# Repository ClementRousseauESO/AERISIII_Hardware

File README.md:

# AERISIII_Hardware
KiCad projects for AERISIII boards

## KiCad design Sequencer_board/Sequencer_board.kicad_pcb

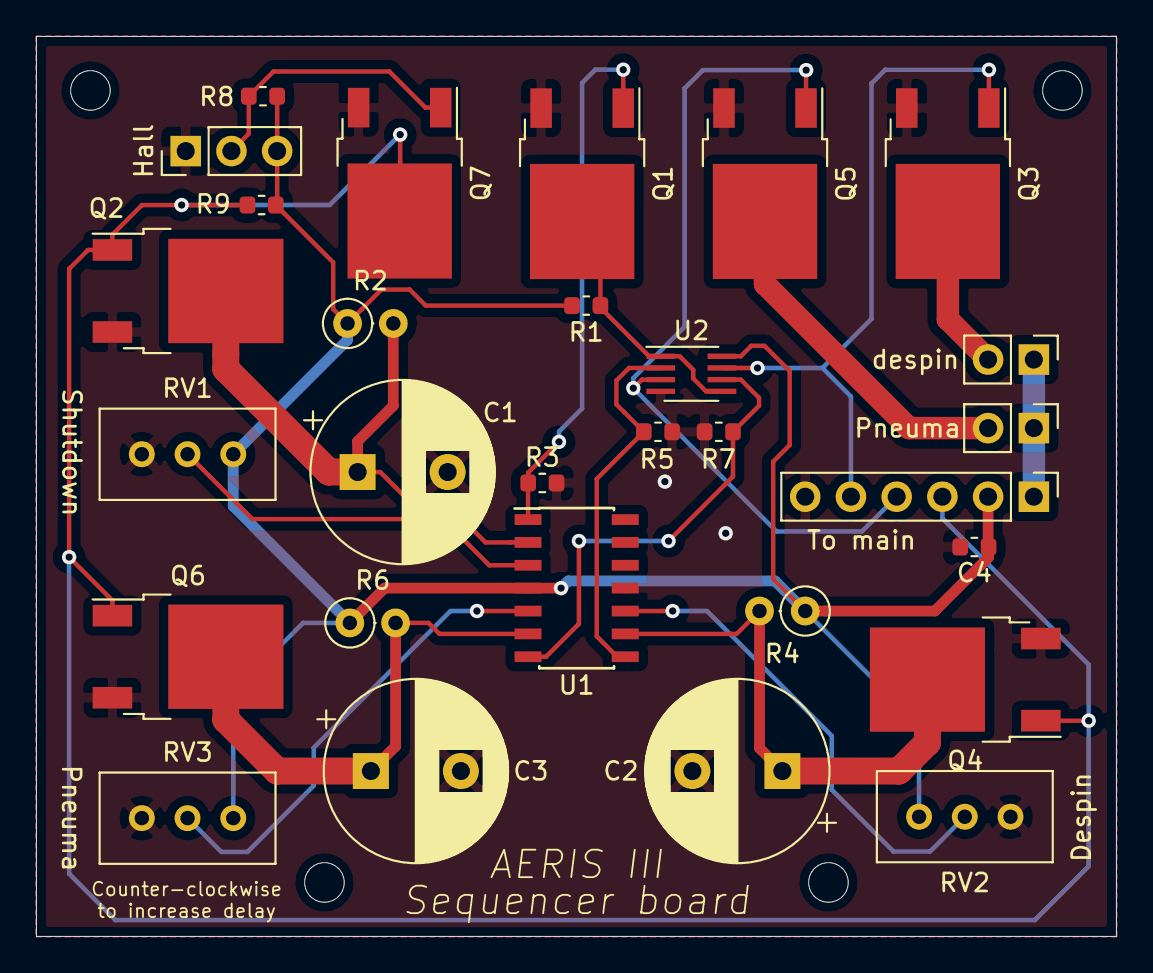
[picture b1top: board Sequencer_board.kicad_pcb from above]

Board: 2 copper layers, 60.0 x 50.0 mm, 29 parts (0 on the bottom side), 19 nets.

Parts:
C1, C2, C3: 470u; CP_Radial_D10.0mm_P5.00mm
C4: 100n; C_0603_1608Metric
Hall: Conn_01x03; PinHeader_1x03_P2.54mm_Vertical
Pneuma: Conn_01x02; PinHeader_1x02_P2.54mm_Vertical
Q1, Q2, Q3, Q4, Q5, Q6, Q7: Q_NMOS_GDS; TO-252-2
R1, R8, R9: 10k; R_0603_1608Metric
R2: 56k; R_Axial_DIN0207_L6.3mm_D2.5mm_P2.54mm_Vertical
R3, R5, R7: 100k; R_0603_1608Metric
R4: 33k; R_Axial_DIN0207_L6.3mm_D2.5mm_P2.54mm_Vertical
R6: 18k; R_Axial_DIN0207_L6.3mm_D2.5mm_P2.54mm_Vertical
RV1, RV2, RV3: 10k; Potentiometer_Bourns_3296W_Vertical
To main: Conn_01x06; PinHeader_1x06_P2.54mm_Vertical
U1: LM324; SOIC-14_3.9x8.7mm_P1.27mm
U2: 74LVC2G08; SSOP-8_2.95x2.8mm_P0.65mm
despin: Conn_01x02; PinHeader_1x02_P2.54mm_Vertical

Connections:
+5V: C4.1, Hall.3, R1.1, R2.1, R4.1, R6.1, R8.1, R9.1, RV1.1, RV2.1, RV3.1, To main.2, U1.4, U2.8
+24V: Pneuma.1, To main.1, despin.1
/AN_shutdown: Q1.2, R1.2, U2.1, U2.5
/despin: Q3.1, To main.5, U2.7
/hall: Q2.1, Q4.1, Q6.1, Q7.2, R9.2, To main.3
/pneuma: Q5.1, To main.4, U2.3
GND: C1.2, C2.2, C3.2, C4.2, Hall.1, Q1.3, Q2.3, Q3.3, Q4.3, Q5.3, Q6.3, Q7.3, R3.2, R5.2, R7.2, RV1.3, RV2.3, RV3.3, To main.6, U1.11, U2.4
unnamed: C1.1, Q2.2, R2.2, U1.2
unnamed: C2.1, Q4.2, R4.2, U1.9
unnamed: C3.1, Q6.2, R6.2, U1.6
unnamed: Hall.2, Q7.1, R8.2
unnamed: Q3.2, despin.2
unnamed: Pneuma.2, Q5.2
unnamed: Q1.1, R3.1, U1.1
unnamed: R5.1, U1.8, U2.2
unnamed: R7.1, U1.7, U2.6
unnamed: RV1.2, U1.3
unnamed: RV2.2, U1.10
unnamed: RV3.2, U1.5

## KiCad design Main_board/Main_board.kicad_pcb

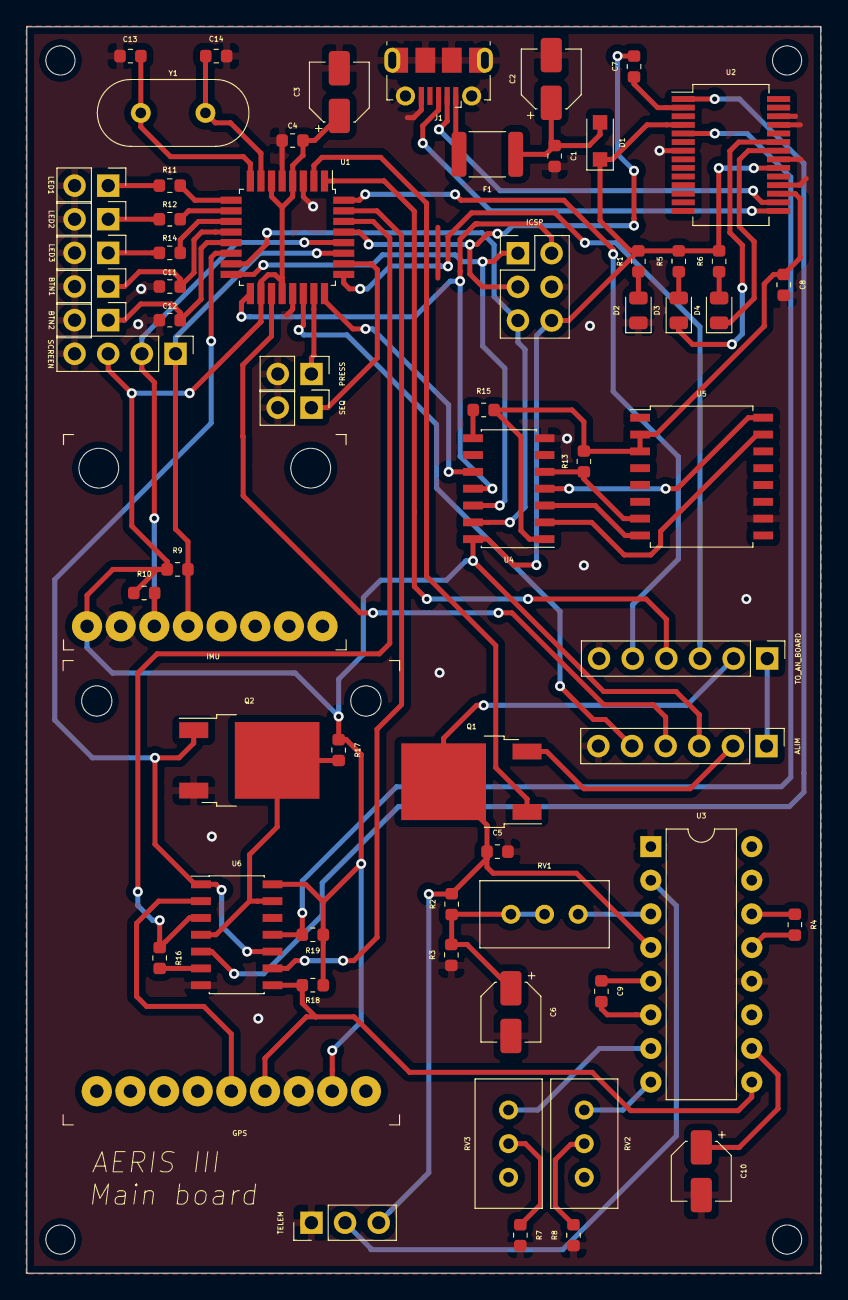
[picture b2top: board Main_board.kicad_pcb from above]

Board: 2 copper layers, 59.9 x 94.1 mm, 65 parts (0 on the bottom side), 67 nets.

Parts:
ALIM: Conn_01x06; PinHeader_1x06_P2.54mm_Vertical
BTN1, BTN2: Conn_01x02; PinHeader_1x02_P2.54mm_Vertical
C1, C4, C5, C7, C8: 100n; C_0603_1608Metric
C2, C3: 4.7u; CP_Elec_4x5.4
C6: 10u; CP_Elec_4x5.4
C9: 4.7n; C_0603_1608Metric
C10: 1u; CP_Elec_4x5.4
C11, C12: 10n; C_0603_1608Metric
C13, C14: 22p; C_0603_1608Metric
D1: D_Schottky; D_SOD-123F
D2, D3, D4: LED; LED_0805_2012Metric
F1: Polyfuse; Fuse_1812_4532Metric
GPS: Conn_01x09; SHIELD_GPS_ADAFRUIT
ICSP: Conn_02x03; PinHeader_2x03_P2.54mm_Vertical
IMU: Conn_01x08; SHIELD_MPU_6050
J1: USB_B_Micro; USB_Micro-B_Molex-105017-0001
LED1, LED2, LED3: Conn_01x02; PinHeader_1x02_P2.54mm_Vertical
PRESS: Conn_01x02; PinHeader_1x02_P2.54mm_Vertical
Q1: Q_PMOS_GDS; TO-252-2
Q2: Q_NMOS_GDS; TO-252-2
R1, R5, R6, R11, R12, R14: 270; R_0603_1608Metric
R2, R3: 5.1k; R_0603_1608Metric
R4: 200; R_0603_1608Metric
R7, R13, R15, R17: 10k; R_0603_1608Metric
R8: 3.6k; R_0603_1608Metric
R9, R10: 5.4k; R_0603_1608Metric
R16: 1k; R_0603_1608Metric
R18, R19: 100k; R_0603_1608Metric
RV1: 50k; Potentiometer_Bourns_3296W_Vertical
RV2: 5k; Potentiometer_Bourns_3296W_Vertical
RV3: 10k; Potentiometer_Bourns_3296W_Vertical
SCREEN: Conn_01x04; PinHeader_1x04_P2.54mm_Vertical
SEQ: Conn_01x02; PinHeader_1x02_P2.54mm_Vertical
TELEM: Conn_01x03; PinHeader_1x03_P2.54mm_Vertical
TO_AN_BOARD: Conn_01x06; PinHeader_1x06_P2.54mm_Vertical
U1: ATmega328-AU; TQFP-32_7x7mm_P0.8mm
U2: FT232RL; SSOP-28_5.3x10.2mm_P0.65mm
U3: XR2206; DIP-16_W7.62mm
U4: TXS0104; SOIC-14_3.9x8.7mm_P1.27mm
U5: MX25L51245G; SOIC-16W_7.5x10.3mm_P1.27mm
U6: 74LS125; SOIC-14_3.9x8.7mm_P1.27mm
Y1: 20Mhz; Crystal_HC49-4H_Vertical

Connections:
+3V3: C8.1, R13.2, R15.2, U2.17, U4.1, U5.2, U5.3
+5V: ALIM.3, C3.1, C4.1, D1.1, GPS.8, ICSP.6, IMU.1, R1.1, R5.2, R6.2, R9.1, R10.1, R17.1, R18.1, R19.1, SCREEN.3, U1.4, U1.6, U1.18, U1.20, U2.4, U2.20, U4.14, U6.14
+12V: C5.1, Q1.2, R2.2, TELEM.3, TO_AN_BOARD.2, U3.4
+24V: ALIM.1, TO_AN_BOARD.1
/12v_on: Q1.1, U1.2
/bat_current: ALIM.5, U1.22
/bat_volt: ALIM.4, U1.19
/btn1: BTN1.1, C11.1, U1.12
/btn2: BTN2.1, C12.1, U1.13
/despin: TO_AN_BOARD.5, U1.32
/flash: U1.24, U4.10
/hall: TO_AN_BOARD.3, U1.25
/led1: R11.2, U1.9
/led2: R12.2, U1.10
/led3: R14.2, U1.11
/miso: ICSP.1, U1.16, U4.12
/mosi: ICSP.5, U1.15, U4.13
/pneuma: TO_AN_BOARD.4, U1.1
/pressure: PRESS.1, U1.23
/reset: C7.2, ICSP.3, U1.29
/rx_mcu: R16.1, U1.30, U6.3
/rx_periph: GPS.6, R18.2, U3.9, U6.8
/rx_usb: R19.2, U2.5, U6.11
/sck: ICSP.2, U1.17, U4.11
/scl: IMU.3, R10.2, SCREEN.2, U1.28
/sda: IMU.4, R9.2, SCREEN.1, U1.27
/seq: SEQ.1, U1.26
/tx_mcu: U1.31, U6.9
/tx_periph: GPS.5, U6.2
/tx_usb: U2.1, U6.5
/uart_off: Q2.2, R17.2, U6.4, U6.13
/uart_on: Q2.1, U1.14, U6.1, U6.10
/xtal1: C14.2, U1.7, Y1.1
/xtal2: C13.2, U1.8, Y1.2
GND: ALIM.6, BTN1.2, BTN2.2, C1.2, C2.2, C3.2, C4.2, C5.2, C6.2, C8.2, C10.2, C11.2, C12.2, C13.1, C14.1, D2.1, GPS.7, ICSP.4, IMU.2, J1.5, J1.6, LED1.2, LED2.2, LED3.2, PRESS.2, Q2.3, R3.1, R7.2, R8.1, SCREEN.4, SEQ.2, TELEM.1, TO_AN_BOARD.6, U1.3, U1.5, U1.21, U2.7, U2.18, U2.21, U2.25, U2.26, U3.1, U3.12, U4.7, U5.10, U6.7
unnamed: ALIM.2, Q1.3
unnamed: C1.1, C2.1, D1.2, F1.1
unnamed: C6.1, R2.1, R3.2, RV1.2, RV1.3
unnamed: C7.1, U2.2
unnamed: C9.1, U3.5
unnamed: C9.2, U3.6
unnamed: C10.1, U3.10
unnamed: D2.2, R1.2
unnamed: D3.1, U2.23
unnamed: D3.2, R5.1
unnamed: D4.1, U2.22
unnamed: D4.2, R6.1
unnamed: F1.2, J1.1
unnamed: J1.2, U2.16
unnamed: J1.3, U2.15
unnamed: LED1.1, R11.1
unnamed: LED2.1, R12.1
unnamed: LED3.1, R14.1
unnamed: R4.1, U3.14
unnamed: R4.2, U3.13
unnamed: R7.1, RV3.2
unnamed: R8.2, RV2.2
unnamed: R13.1, U4.5, U5.7
unnamed: R15.1, U4.8
unnamed: R16.2, U6.6
unnamed: RV1.1, U3.3
unnamed: RV2.1, U3.8
unnamed: RV3.1, U3.7
unnamed: TELEM.2, U3.2
unnamed: U4.2, U5.15
unnamed: U4.3, U5.8
unnamed: U4.4, U5.16

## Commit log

2019-04-21 ENH: Add first design bricks - ATmega328 with decoupling resistors - Utilities (cristal, icsp, uart and gates) - IHM connectors (screen, buttons and leds) - Shields connectors - AN board connector - 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
2019-04-23 ENH: Added VCO, voltage translator and flash chip libs and associated circuits
2019-04-26 ENH: Added 12v_on + usb to ttl circuit
2019-04-26 ENH: Added UART multichannel handling + style update
2019-05-02 ENH: Added most of the footprints (GPS+IMU remaining) + added 5v led
2019-05-03 ENH: Added GPS module footprint
2019-05-03 ENH: Added MPU6050 footprint
2019-05-03 ENH: Last BOM + footprint update before V0-2
2019-05-05 ENH: Component placed
2019-05-27 WIP: routing
2019-05-31 WIP: still routing
2019-05-31 ENH: finished routing
2019-06-01 ENH: Added gerber output
2019-06-16 ENH: Added Sequencer board
2019-07-01 ENH: Started AN board schema
2019-07-10 ENH: AN board finished

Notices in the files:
Main_board/Main_board.kicad_pcb:
License: MIT license
Sequencer_board/Sequencer_board.kicad_pcb:
License: MIT
